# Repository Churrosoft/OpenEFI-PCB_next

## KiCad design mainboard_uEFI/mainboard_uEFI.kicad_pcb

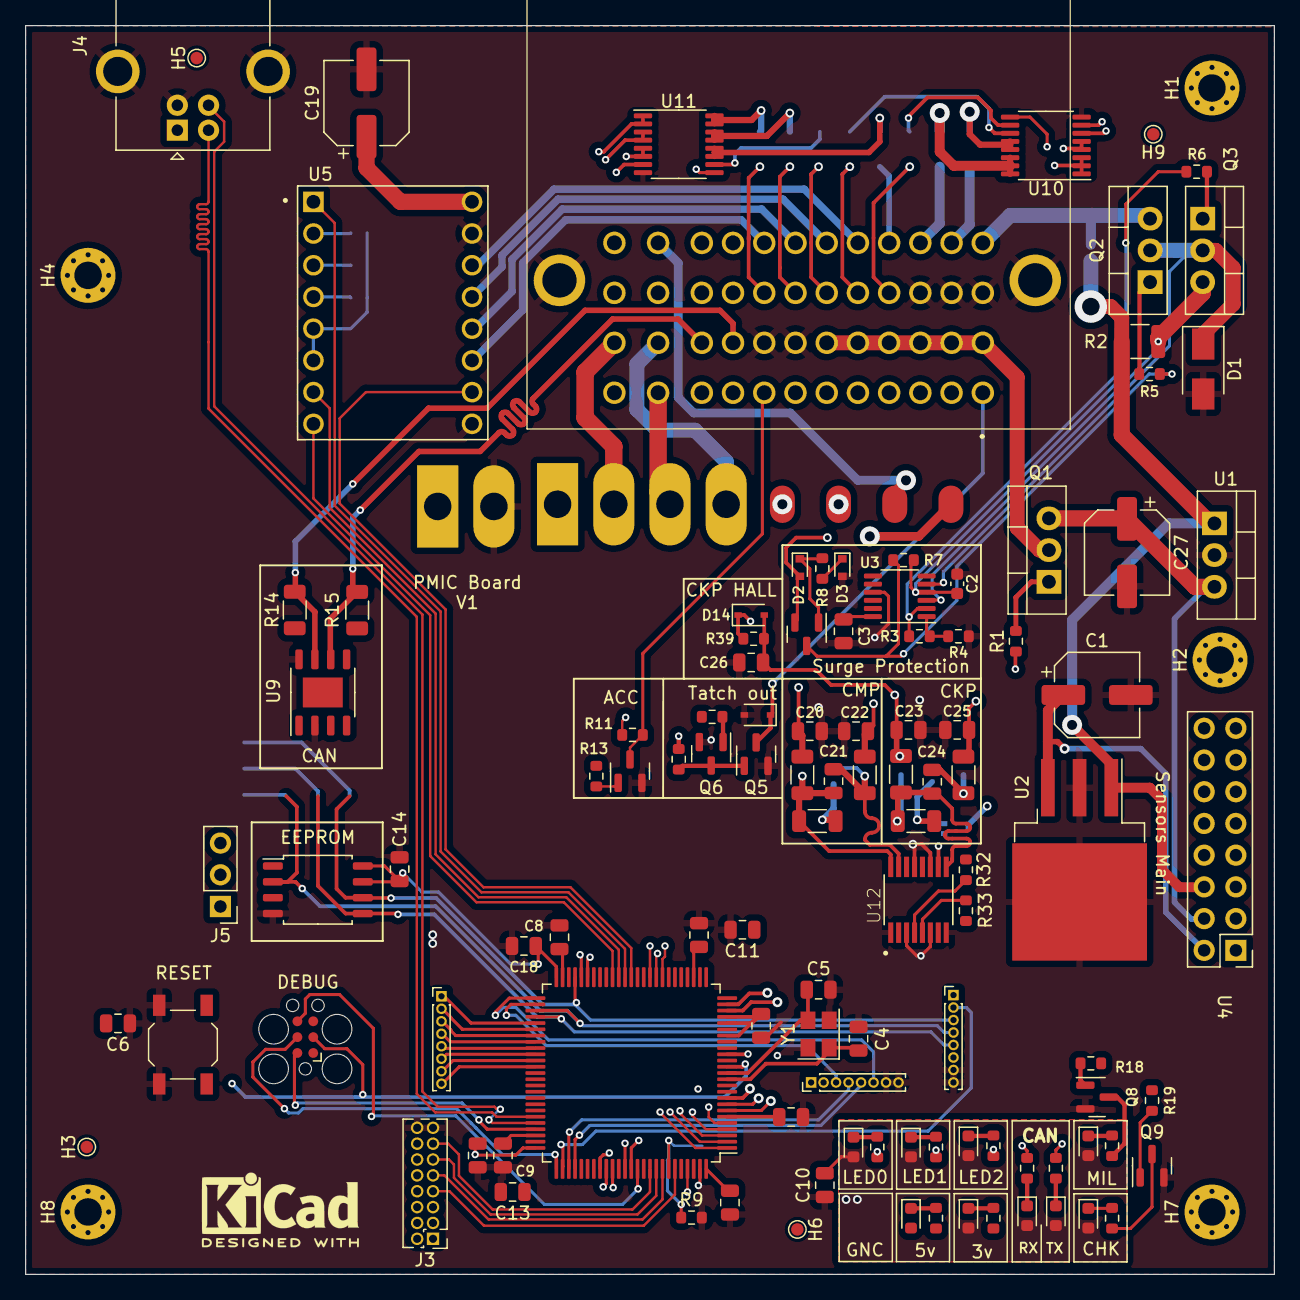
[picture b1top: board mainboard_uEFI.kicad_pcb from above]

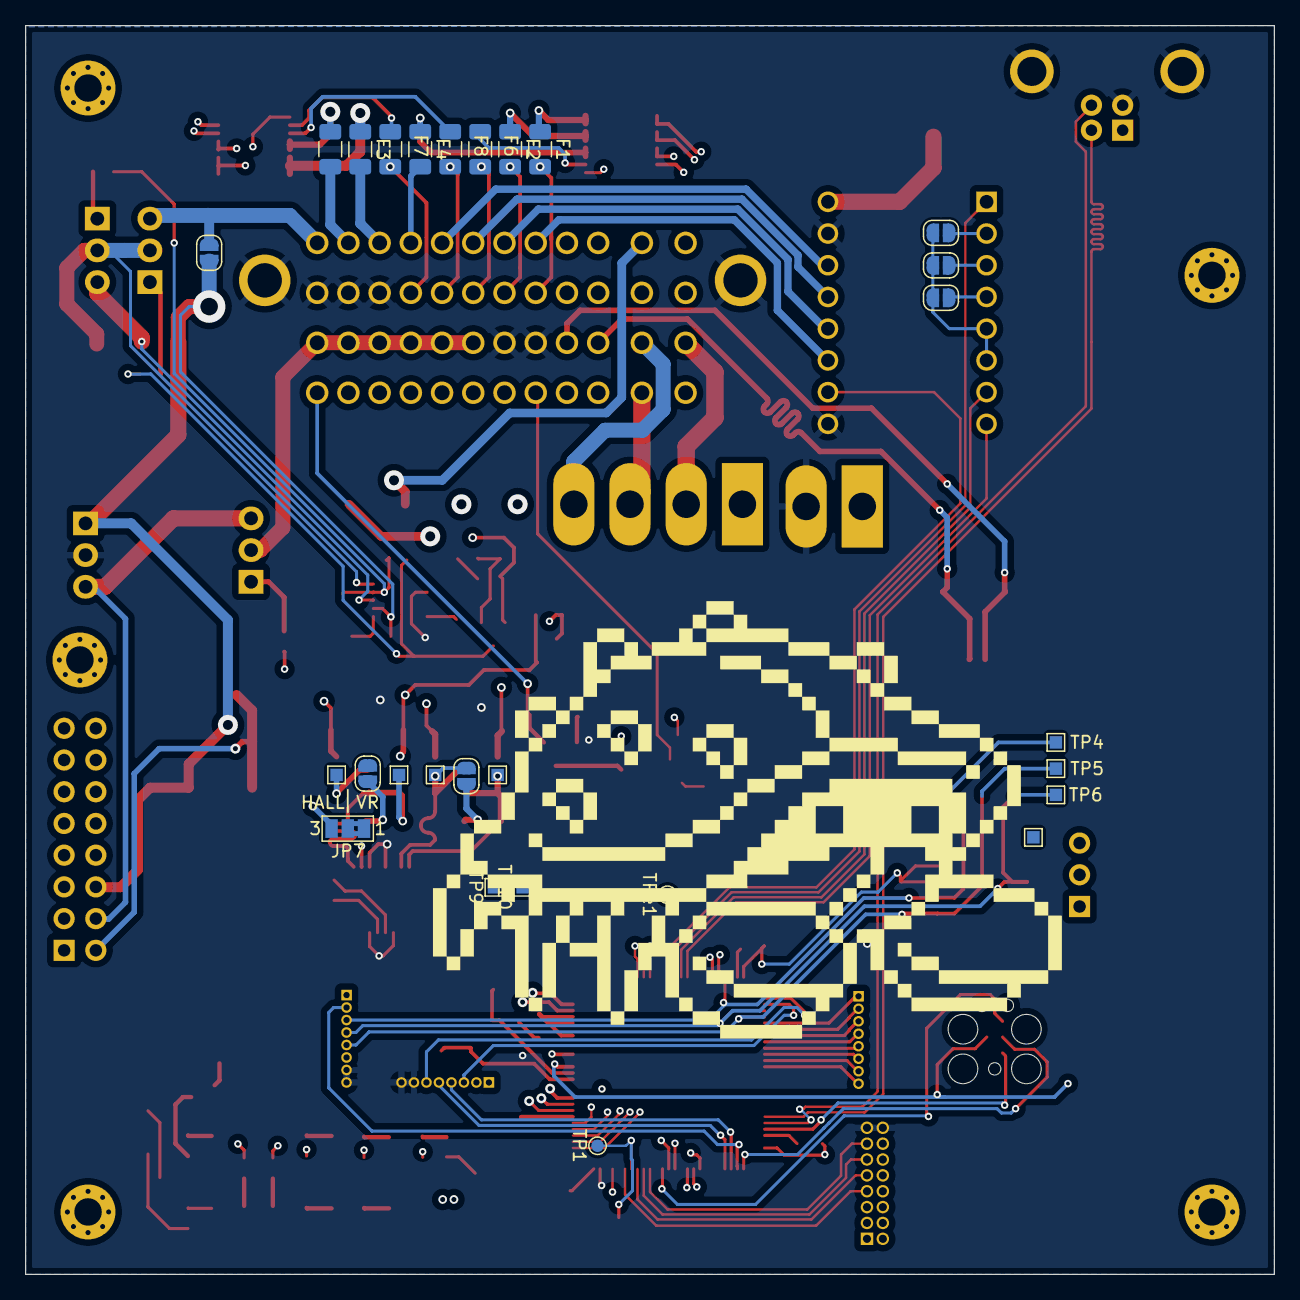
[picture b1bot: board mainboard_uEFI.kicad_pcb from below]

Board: 4 copper layers, 100.0 x 100.0 mm, 141 parts (27 on the bottom side), 143 nets.

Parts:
C1, C19, C27: 100uF ±20% 35V; CP_Elec_6.3x7.7
C2: 47nF; C_0603_1608Metric
C3, C6, C7, C10, C12, C13, C14, C15, C16, C17: 100nF; C_0805_2012Metric
C4, C5: 15pF; C_0805_2012Metric
C8, C9: 2.2uF; C_0805_2012Metric
C11: 1uF; C_0805_2012Metric
C18: 4.7uF; C_0805_2012Metric
C20, C21, C22, C23, C24, C25, C26: 0.01uF; C_0805_2012Metric
D1: SMAJ58CA; D_SMA
D2, D3: 1N4148; D_SOD-523
D4: MM3Z24VT1G; D_SOD-323
D5, D6, D7, D8, D9, D10, D11, D12, D13: LED; LED_0603_1608Metric
D14: K26; D_SOD-323
F1, F2, F3, F4, F5, F6, F7, F8: 750mA; Fuse_1206_3216Metric
H1, H2, H4, H7, H8: MountingHole; MountingHole_2.2mm_M2_Pad_Via
H3, H5, H6, H9: MountingHole; TestPoint_Pad_D1.0mm
J1: 36638-0002; 366380002
J2: Tag connect; Tag-Connect_TC2030-IDC-FP_2x03_P1.27mm_Vertical
J3: Conn_02x08_Odd_Even; PinHeader_2x08_P1.27mm_Vertical
J4: USB_B; USB_B_OST_USB-B1HSxx_Horizontal
J5: Conn_01x03; PinHeader_1x03_P2.54mm_Vertical
JP1: Jumper_NO_Small; SolderJumper-2_P1.3mm_Open_RoundedPad1.0x1.5mm
JP2, JP3, JP4, JP5, JP6: SolderJumper_2_Open; SolderJumper-2_P1.3mm_Open_RoundedPad1.0x1.5mm
JP7: vr/hall; SolderJumper-3_P1.3mm_Bridged2Bar12_Pad1.0x1.5mm_NumberLabe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
Q1: IRF540N; TO-220-3_Vertical
Q2, Q3: IRLZ44N; TO-220-3_Vertical
Q4, Q6, Q8, Q9: SS8050; SOT-23
Q5, Q7: AO3400A; SOT-23
R1, R5, R6: 10R 1/10W; R_0603_1608Metric
R2: 0.01R; R_1210_3225Metric
R3: 57.6K 1/10W; R_0603_1608Metric
R4: 4.99K 1/10W; R_0603_1608Metric
R7: 1M 1/10W; R_0603_1608Metric
R8: 10K 1/10W; R_0603_1608Metric
R9, R11, R13, R32, R33, R39: 10k; R_0603_1608Metric
R10: 100k; R_0603_1608Metric
R12, R18, R19: 1k; R_0603_1608Metric
R14, R15: 120R; R_1206_3216Metric
R16, R17, R20, R21, R22, R23, R24, R25, R26: 4.7k; R_0603_1608Metric
R27, R30, R34, R37: 10K 1/2W; R_1206_3216Metric
R29, R36: 4.99K 1/2W; R_1206_3216Metric
SW1: SW_Push; SW_SPST_TL3342
SYM1: SYM_Hot_Small; KiCad-Logo2_5mm_SilkScreen
TP1: BOOT0; TestPoint_Pad_D1.0mm
TP2, TP4, TP5, TP6, TP7, TP8, TP9, TP10, TP11, TP12: TestPoint; TestPoint_Pad_1.0x1.0mm
TPe1: BOOT1; TestPoint_Pad_D1.0mm
U1: MIC2940A-5.0WT; TO-220-3_Vertical
U2: MIC2940A-3.3WU; TO-263-3_TabPin2
U3: LT4363IMS; MSOP-12_3x4mm_P0.65mm
U4: SensorsV1
U5: PaP_Driver_v1; IC_DRV8825_STEPPER_MOTOR_DRIVER_CARRIER
U6: 25LCxxx; SOIC-8_5.275x5.275mm_P1.27mm
U7: PMIC_V1; pmic_v1
U8: STM32F407VGTx; LQFP-100_14x14mm_P0.5mm
U9: TJA1042T3118; HTSOP-8-1EP_3.9x4.9mm_P1.27mm_EP2.4x3.2mm
U10, U11: TPL7407LAPWR; TSSOP-16_4.4x5mm_P0.65mm
U12: MAX9926UAEE+; SOP63P602X175-16N
Y1: 25MHz; Crystal_SMD_3225-4Pin_3.2x2.5mm

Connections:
5V_ENABLE: R1.1, U8.16 (PC1)
+3V3: C1.1, C7.1, C10.1, C11.1, C12.1, C13.1, C14.1, C15.1, C16.1, C17.1, C18.1, D5.2 (A), D6.2 (A), D8.2 (A), D9.2 (A), D10.2 (A), D11.2 (A), D12.2 (A), D13.2 (A), D14.1 (K), J2.1, J3.1, JP2.1 (A), JP3.1 (A), JP4.1 (A), R11.1, R32.1, R33.1, R39.1, U2.3 (OUT), U5.5 (RESET), U5.6 (SLEEP), U6.3 (~WP), U6.7 (~HOLD), U6.8 (VCC), U7.34 (3v3), U8.6 (VBAT), U8.11 (VDD), U8.19 (VDD), U8.21 (VREF+), U8.22 (VDDA), U8.28 (VDD), U8.50 (VDD), U8.75 (VDD), U8.100 (VDD), U9.5 (VIO)
+5V: C27.1, D7.2 (A), J3.2, Q1.3 (S), U1.3 (OUT), U9.3 (VCC), U12.14 (VCC)
+5VA: J1.A2, J1.B2, J1.C2, J1.D2, J1.E2, J1.F2, Q1.2 (D)
+12V: C19.1, JP1.2, R2.1, R3.1, R10.1, U1.1 (IN), U2.1 (IN), U3.2 (OUT), U5.16 (VMOT), U7.1 (12v), U7.19 (12v), U7.20 (12v), U10.9 (COM), U11.9 (COM)
+12VA: D2.2 (A), J1.A4, JP1.1, Q2.3 (S), Q4.2 (E)
/ACC_DET: R13.1, U8.80 (PC12)
/AUX_CS_1: J3.3, U8.45 (PE14)
/AUX_CS_2: J3.5, U8.46 (PE15)
/AUX_IN_1: J3.7, U8.95 (PB8)
/AUX_IN_2: J3.9, U8.93 (PB7)
/AUX_IN_3: J3.11, U8.92 (PB6)
/AUX_IN_4: J3.13, U8.91 (PB5)
/AUX_OUT_1: J3.10, U8.35 (PB0)
/AUX_OUT_2: J3.12, U8.34 (PC5)
/AUX_OUT_3: J3.14, U8.33 (PC4)
/CAN1_RX: U8.81 (PD0), U9.4 (RXD)
/CAN1_TX: U8.82 (PD1), U9.1 (TXD)
/CHK: Q9.3 (C), R17.2
/CHK_OUT: R19.1, U8.66 (PC9)
/CKP_D: JP7.2 (C), U8.63 (PC6)
/CKP_VR: JP7.1 (A), R32.2, TP9.1, U12.4 (COUT1)
/CMP: R33.2, TP10.1, U8.64 (PC7), U12.5 (COUT2)
/ECN1: U7.15 (0_c), U8.59 (PD12)
/ECN2: U7.16 (1_c), U8.60 (PD13)
/ECN3: U7.17 (2_c), U8.61 (PD14)
/ECN4: U7.18 (3_c), U8.62 (PD15)
/IN1_N: C21.2, JP5.1 (A), R30.2, TP8.1, U12.15 (IN1-)
/IN1_P: C21.1, R27.2, R29.1, TP7.1, U12.16 (IN1+)
/IN2+: C24.1, R34.2, R36.1, TP11.1, U12.9 (IN2+)
/IN2-: C24.2, JP6.1 (A), R37.2, TP12.1, U12.10 (IN2-)
/INY1: U7.11 (0_c), U8.55 (PD8)
/INY2: U7.12 (1_c), U8.56 (PD9)
/INY3: U7.13 (2_c), U8.57 (PD10)
/INY4: U7.14 (3_c), U8.58 (PD11)
/LED0: R22.2, U8.83 (PD2)
/LED1: R23.2, U8.84 (PD3)
/LED2: R24.2, U8.85 (PD4)
/LED_CAN_RX: R26.2, U8.87 (PD6)
/LED_CAN_TX: R25.2, U8.88 (PD7)
/MEMORY_CS: TP2.1, U6.1 (~CS), U8.44 (PE13)
/MIL: Q8.3 (C), R16.2
/MIL_OUT: R18.1, U8.65 (PC8), U10.7 (IN7)
/MTR_DIR: U5.8 (DIR), U8.41 (PE10)
/MTR_ENABLE: U5.1 (ENABLE), U8.39 (PE8)
/MTR_FAULT: U5.10 (FAULT), U8.38 (PE7)
/MTR_STEP: U5.7 (STEP), U8.40 (PE9)
/NRST: C6.2, J2.3, SW1.1, U8.14 (NRST)
/PMIC_CS: U7.33 (SPI_CS), U8.77 (PA15)
/PMIC_ENABLE: U7.24 (ENABLE), U8.51 (PB12)
/PMIC_MAXI: U7.23 (MAXI), U8.79 (PC11)
/PMIC_NOMI: U7.22 (NOMI), U8.78 (PC10)
/PMIC_SPARK: U7.21 (SPARK), U8.52 (PB13)
/PWM | Relays /CHECK_ENGINE: F8.1, U10.11 (OUT6)
/PWM | Relays /MIL_OUT: F7.1, U10.10 (OUT7)
/PWM | Relays /R3_OUT: F6.1, U11.10 (OUT7)
/RPM_OUT: R12.1, U8.42 (PE11)
/R_AAC: U8.3 (PE4), U11.1 (IN1), U11.2 (IN2)
/R_ECN_INY: U8.1 (PE2), U11.5 (IN5), U11.6 (IN6)
/R_GNC_GLP: U8.2 (PE3), U11.3 (IN3), U11.4 (IN4)
/R_LMB: U8.97 (PE0), U11.7 (IN7)
/SPI2_MISO: J3.6, J5.3, TP6.1, U6.2 (MISO), U7.31 (SPI_MISO), U8.53 (PB14)
/SPI2_MOSI: J3.8, J5.2, TP5.1, U6.5 (MOSI), U7.30 (SPI_MOSI), U8.54 (PB15)
/SPI2_SCK: J3.4, J5.1, TP4.1, U6.6 (SCK), U7.32 (SPI_CLK), U8.47 (PB10)
/SYS_SWCLK: J2.4, U8.76 (PA14)
/SYS_SWDIO: J2.2, U8.72 (PA13)
/SYS_SWO: J2.6, U8.89 (PB3)
/TIM9_CH1: U8.4 (PE5), U10.1 (IN1), U10.2 (IN2), U10.3 (IN3)
/TIM9_CH2: U8.5 (PE6), U10.4 (IN4), U10.5 (IN5)
/USB_D+: J4.3 (D+), U8.71 (PA12)
/USB_D-: J4.2 (D-), U8.70 (PA11)
/VBUS: J4.1 (VBUS), U8.68 (PA9)
A1: D4.1 (K), J1.A1, Q5.3 (D)
B4: F5.2, J1.B4
C4: F3.2, J1.C4
CAN+: J1.J2, R14.2, U9.7 (CANH)
CAN-: J1.K2, R15.2, U9.6 (CANL)
CKP+: C23.1, C26.1, D14.2 (A), J1.K4, JP7.3 (B), R34.1, R39.2
CKP-: C25.1, J1.J4, R37.1
CMP+: C20.1, J1.K3, R27.1
CMP-: C22.1, J1.J3, R30.1
D3: F7.2, J1.D3
D4: F4.2, J1.D4
E3: F8.2, J1.E3
E4: J1.E4, U5.14 (B2)
F3: F6.2, J1.F3
F4: J1.F4, U5.13 (B1)
G3: F2.2, J1.G3
G4: J1.G4, U5.12 (A1)
GND: C1.2, C2.2, C3.2, C4.2, C5.2, C6.1, C7.2, C8.2, C9.2, C10.2, C11.2, C12.2, C13.2, C14.2, C15.2, C16.2, C17.2, C18.2, C19.2, C20.2, C22.2, C23.2, C25.2, C26.2, C27.2, D1.2 (A2), D3.2 (A), D4.2 (A), J1.A3, J1.B3, J1.C3, J1.G2, J1.H2, J1.MH1, J1.MH2, J2.5, J3.15, J3.16, J4.4 (GND), J4.5 (Shield), Q5.2 (S), Q6.2 (E), Q7.2 (S), Q8.2 (E), Q9.2 (E), R4.1, R9.2, R20.2, R21.2, SW1.2, U1.2 (GND), U2.2 (GND), U3.9 (GND), U5.9 (GND), U5.15 (GND), U6.4 (GND), U7.2 (GND), U7.25 (GND), U7.26 (GND), U7.27 (GND), U7.28 (GND), U8.10 (VSS), U8.20 (VSSA), U8.27 (VSS), U8.74 (VSS), U8.99 (VSS), U9.2 (GND), U9.8 (STB), U10.8 (GND), U11.8 (GND), U12.1 (INT_THRS1), U12.3 (BIAS1), U12.6 (BIAS2), U12.8 (INT_THRS2), U12.11 (GND), U12.13 (ZERO_EN), Y1.2, Y1.4
H1: J1.H1, Q7.3 (D), R11.2
H3: F1.2, J1.H3
H4: J1.H4, U5.11 (A2)
L1: J1.L1, U7.5 (2)
L2: J1.L2, U7.6 (3)
L3: J1.L3, U7.10 (3)
L4: J1.L4, U7.9 (2)
M1: J1.M1, U7.3 (0)
M2: J1.M2, U7.4 (1)
M3: J1.M3, U7.8 (1)
M4: J1.M4, U7.7 (0)
unnamed: C2.1, R6.2, R7.1, U3.4 (GATE)
unnamed: C3.1, U3.12 (TMR)
unnamed: C8.1, U8.49 (VCAP_1)
unnamed: C9.1, U8.73 (VCAP_2)
unnamed: D1.1 (A1), Q2.2 (D), Q3.2 (D), U3.5 (VCC)
unnamed: D2.1 (K), Q4.1 (B), R8.1
unnamed: D3.1 (K), R8.2
unnamed: D5.1 (K), R16.1
unnamed: D6.1 (K), R17.1
unnamed: D7.1 (K), R20.1
unnamed: D8.1 (K), R21.1
unnamed: D9.1 (K), R22.1
unnamed: D10.1 (K), R23.1
unnamed: D11.1 (K), R24.1
unnamed: D12.1 (K), R25.1
unnamed: D13.1 (K), R26.1
unnamed: F1.1, U11.15 (OUT2), U11.16 (OUT1)
unnamed: F2.1, U11.13 (OUT4), U11.14 (OUT3)
unnamed: F3.1, U10.14 (OUT3), U10.15 (OUT2), U10.16 (OUT1)
unnamed: F4.1, U11.11 (OUT6), U11.12 (OUT5)
unnamed: F5.1, U10.12 (OUT5), U10.13 (OUT4)
unnamed: JP2.2 (B), U5.2 (M0)
unnamed: JP3.2 (B), U5.3 (M1)
unnamed: JP4.2 (B), U5.4 (M2)
unnamed: JP5.2 (B), R29.2
unnamed: JP6.2 (B), R36.2
unnamed: Q1.1 (G), R1.2
unnamed: Q2.1 (G), R5.1
unnamed: Q3.1 (G), R6.1
unnamed: Q3.3 (S), R2.2, U3.3 (SNS)
unnamed: Q4.3 (C), R5.2, R7.2
unnamed: Q5.1 (G), Q6.3 (C), R10.2
unnamed: Q6.1 (B), R12.2
unnamed: Q7.1 (G), R13.2
unnamed: Q8.1 (B), R18.2
unnamed: Q9.1 (B), R19.2
unnamed: R3.2, R4.2, U3.1 (FB)
unnamed: R9.1, TP1.1, U8.94 (BOOT0)
unnamed: R14.1, R15.1
unnamed: TPe1.1, U8.37 (PB2)
OSC_IN: C4.1, U8.12 (PH0), Y1.1
OSC_OUT: C5.1, U8.13 (PH1), Y1.3

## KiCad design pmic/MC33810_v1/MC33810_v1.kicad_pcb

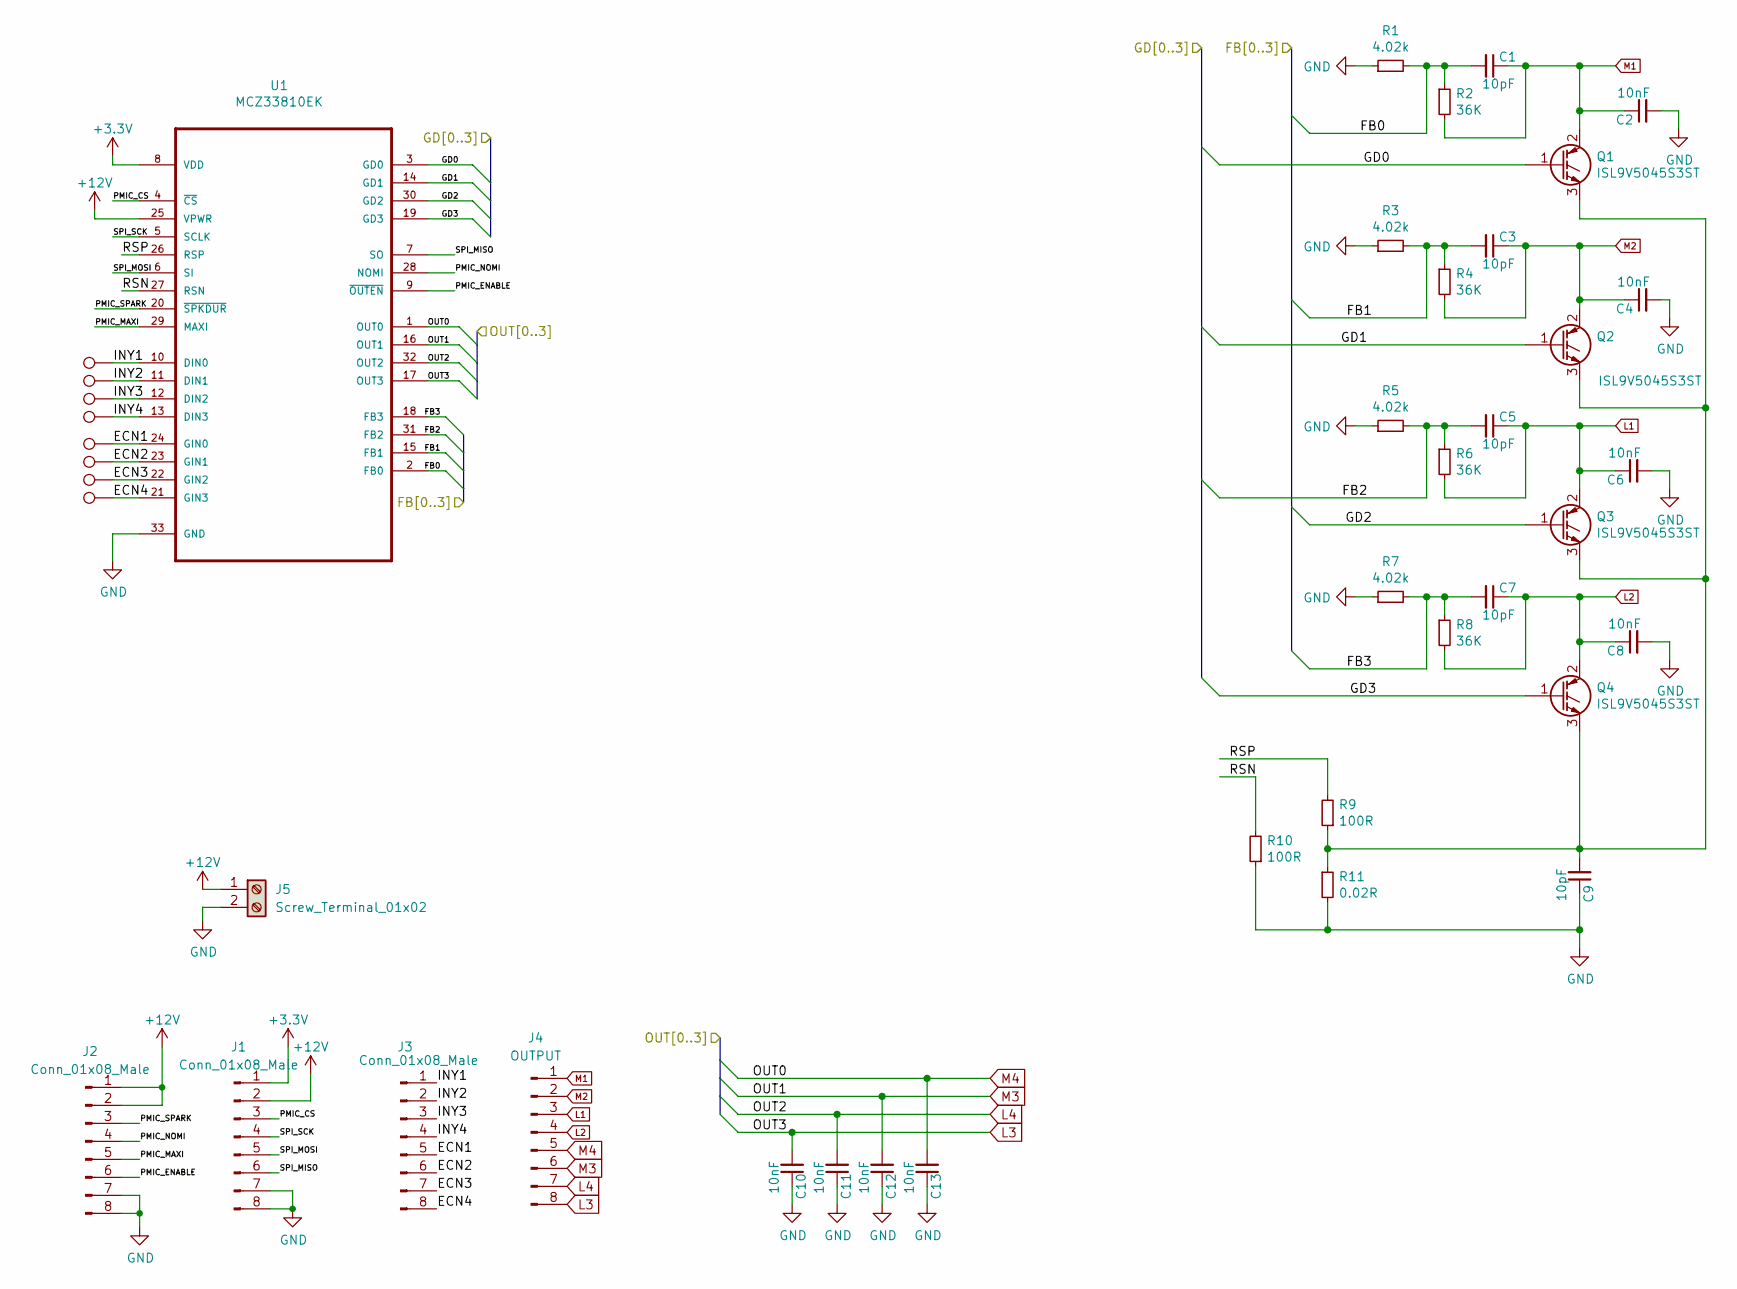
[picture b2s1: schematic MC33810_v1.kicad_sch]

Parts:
C1, C3, C5, C7: 10pF; C_0603_1608Metric; LCSC C106245
C2, C4, C6, C8, C10, C11, C12, C13: 10nF; C_0603_1608Metric; LCSC C100042
C9: 10pF; C_0603_1608Metric
J1, J2, J3: Conn_01x08_Male; PinHeader_1x08_P1.00mm_Vertical
J4: OUTPUT; TerminalBlock_Dinkle_DT-55-B01X-08_P10.00mm
J5: Screw_Terminal_01x02; TerminalBlock_Dinkle_DT-55-B01X-02_P10.00mm
Q1, Q2, Q3, Q4: ISL9V5045S3ST; TO-263-2
R1, R3, R5, R7: 4.02k; R_0603_1608Metric; LCSC C23040
R2, R4, R6, R8: 36K; R_0603_1608Metric; LCSC C192548
R9, R10: 100R; R_0603_1608Metric; LCSC C159890
R11: 0.02R; R_2512_6332Metric; LCSC C326611
TP1, TP2, TP3, TP4, TP5, TP6, TP7, TP8: TestPoint; TestPoint_Pad_1.0x1.0mm
U1: MCZ33810EK; SOP65P1030X245-33N

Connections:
+3V3: J1.1, U1.8 (VDD)
+12V: J1.2, J2.1, J2.2, J5.1, U1.25 (VPWR)
/ECN1: J3.5, TP5.1, U1.24 (GIN0)
/ECN2: J3.6, TP6.1, U1.23 (GIN1)
/ECN3: J3.7, TP7.1, U1.22 (GIN2)
/ECN4: J3.8, TP8.1, U1.21 (GIN3)
/FB0: C1.2, R1.2, R2.1, U1.2 (FB0)
/FB1: C3.2, R3.2, R4.1, U1.15 (FB1)
/FB2: C5.2, R5.2, R6.1, U1.31 (FB2)
/FB3: C7.2, R7.2, R8.1, U1.18 (FB3)
/GD0: Q1.1 (G), U1.3 (GD0)
/GD1: Q2.1 (G), U1.14 (GD1)
/GD2: Q3.1 (G), U1.30 (GD2)
/GD3: Q4.1 (G), U1.19 (GD3)
/INY1: J3.1, TP1.1, U1.10 (DIN0)
/INY2: J3.2, TP2.1, U1.11 (DIN1)
/INY3: J3.3, TP3.1, U1.12 (DIN2)
/INY4: J3.4, TP4.1, U1.13 (DIN3)
/PMIC_CS: J1.3, U1.4 (~CS)
/PMIC_ENABLE: J2.6, U1.9 (~OUTEN)
/PMIC_MAXI: J2.5, U1.29 (MAXI)
/PMIC_NOMI: J2.4, U1.28 (NOMI)
/PMIC_SPARK: J2.3, U1.20 (~SPKDUR)
/RSN: R10.2, U1.27 (RSN)
/RSP: R9.2, U1.26 (RSP)
/SPI_MISO: J1.6, U1.7 (SO)
/SPI_MOSI: J1.5, U1.6 (SI)
/SPI_SCK: J1.4, U1.5 (SCLK)
GND: C2.2, C4.2, C6.2, C8.2, C9.1, C10.1, C11.1, C12.1, C13.1, J1.7, J1.8, J2.7, J2.8, J5.2, R1.1, R3.1, R5.1, R7.1, R10.1, R11.2, U1.33 (GND)
L1: C5.1, C6.1, J4.3, Q3.2 (C), R6.2
L2: C7.1, C8.1, J4.4, Q4.2 (C), R8.2
L3: C10.2, J4.8, U1.17 (OUT3)
L4: C11.2, J4.7, U1.32 (OUT2)
M1: C1.1, C2.1, J4.1, Q1.2 (C), R2.2
M2: C3.1, C4.1, J4.2, Q2.2 (C), R4.2
M3: C12.2, J4.6, U1.16 (OUT1)
M4: C13.2, J4.5, U1.1 (OUT0)
unnamed: C9.2, Q1.3 (E), Q2.3 (E), Q3.3 (E), Q4.3 (E), R9.1, R11.1

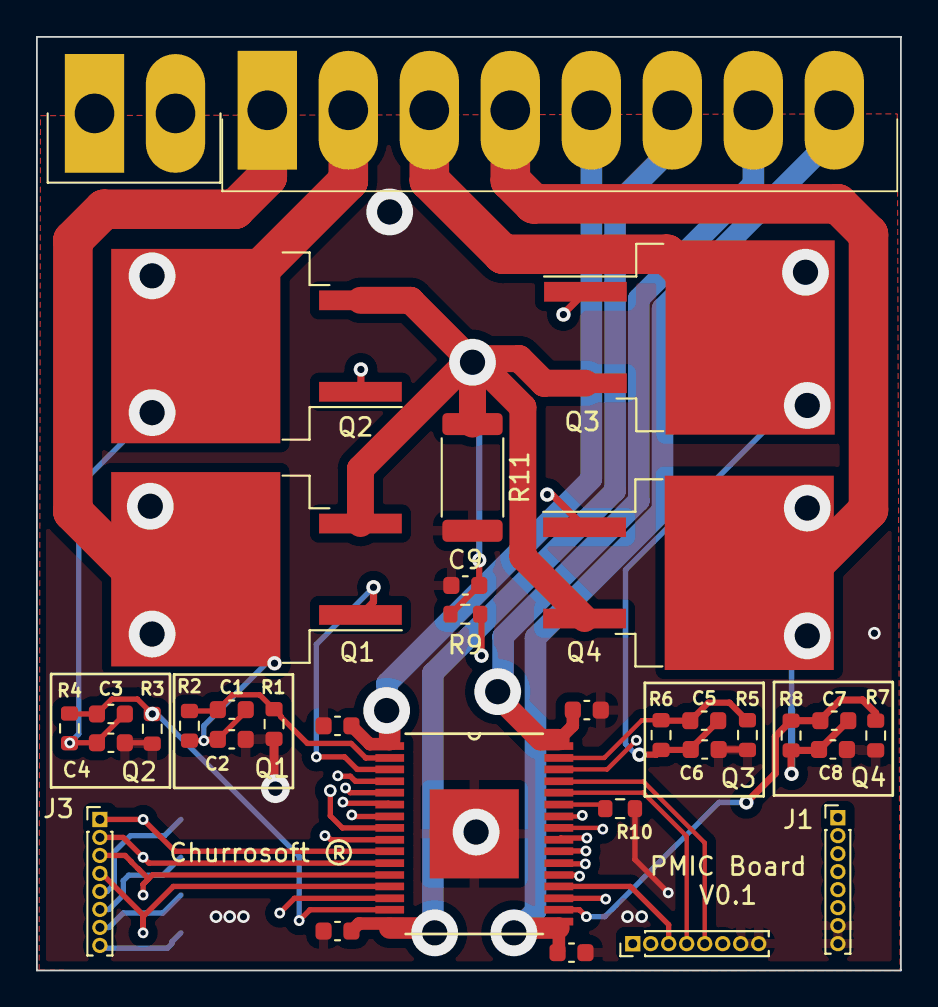
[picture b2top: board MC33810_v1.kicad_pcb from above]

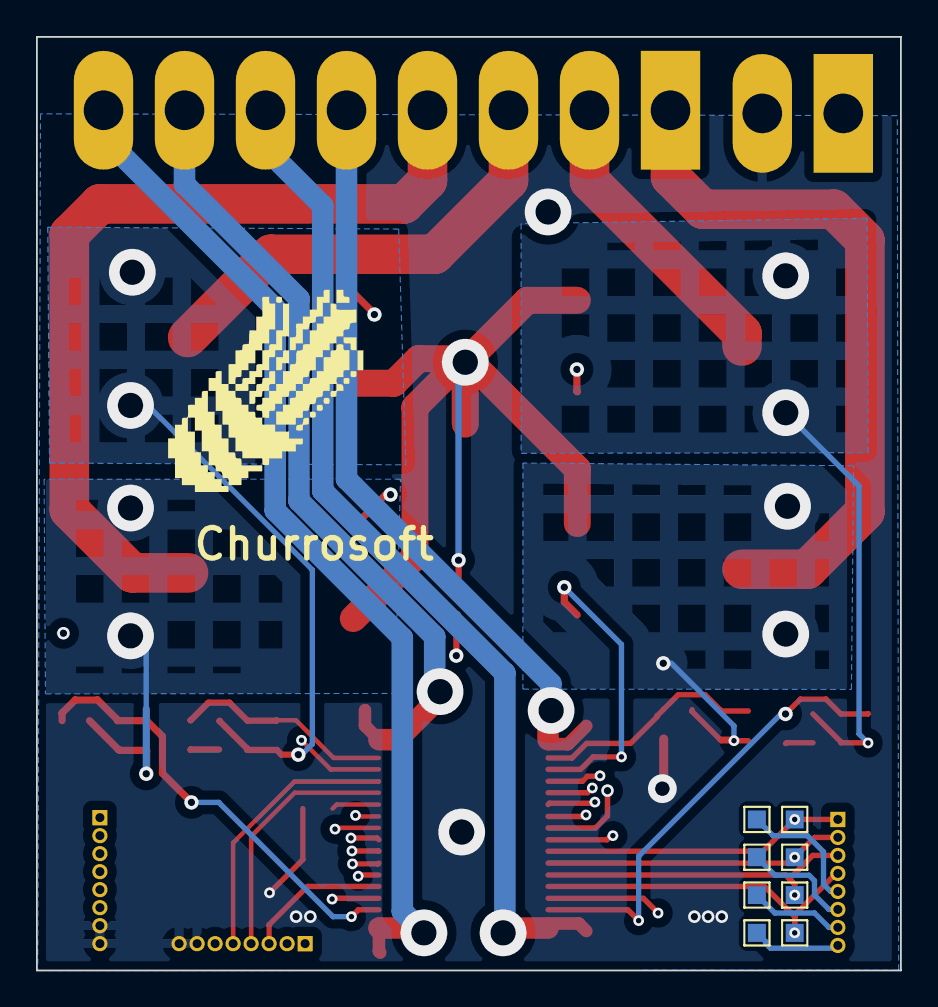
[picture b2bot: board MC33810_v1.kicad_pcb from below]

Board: 4 copper layers, 48.0 x 51.9 mm, 43 parts (9 on the bottom side), 38 nets.

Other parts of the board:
Churrosoft: SYM_Hot_Large; churro_new_v4

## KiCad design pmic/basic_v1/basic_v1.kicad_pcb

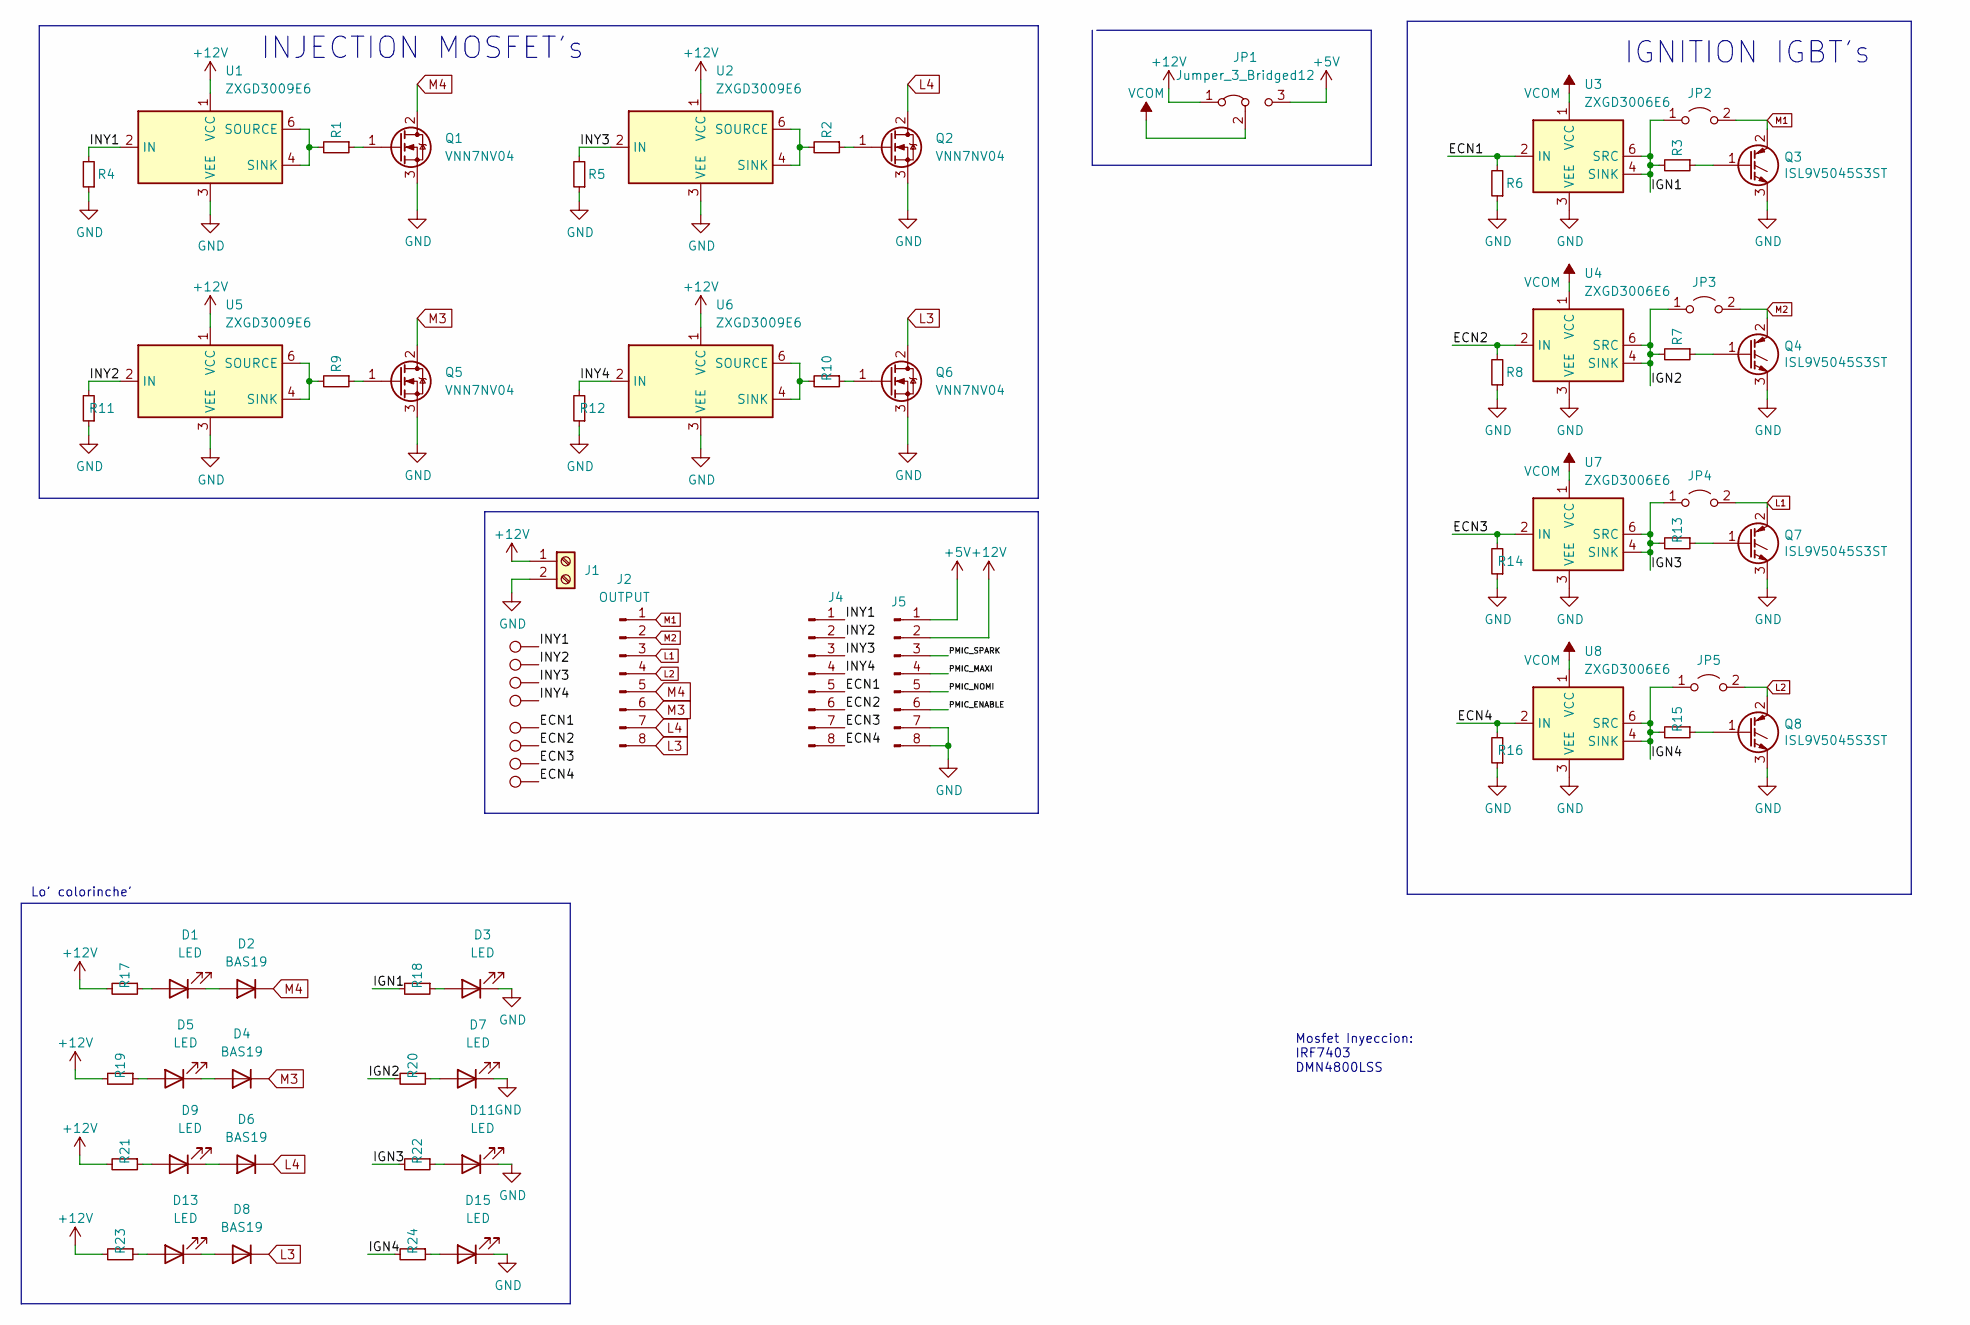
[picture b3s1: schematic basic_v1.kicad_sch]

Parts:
D1, D3, D5, D7, D9, D11, D13, D15: LED; LED_0603_1608Metric
D2, D4, D6, D8: BAS19; SOT-23; LCSC C8661
J1: Screw_Terminal_01x02; TerminalBlock_Dinkle_DT-55-B01X-02_P10.00mm
J2: OUTPUT; hipower_8pin
J4, J5: Conn_01x08_Male; PinHeader_1x08_P1.00mm_Vertical
JP1: Jumper_3_Bridged12; PinHeader_1x03_P2.54mm_Vertical
JP2, JP3, JP4, JP5: Jumper_2_Open; SolderJumper-2_P1.3mm_Open_RoundedPad1.0x1.5mm
Q1, Q2, Q5, Q6: VNN7NV04; TO-252-2; LCSC C155605
Q3, Q4, Q7, Q8: ISL9V5045S3ST; TO-263-2
R1, R2, R3, R7, R9, R10, R13, R15: 22R; R_0805_2012Metric
R4, R5, R6, R8, R11, R12, R14, R16: 100k 1/10W +-1%; R_0603_1608Metric; LCSC C217840
R17, R18, R19, R20, R21, R22, R23, R24: 680R; R_0603_1608Metric; LCSC C217840
TP1, TP2, TP3, TP4, TP5, TP6, TP7, TP8: TestPoint; TestPoint_Pad_1.0x1.0mm
U1, U2, U5, U6: ZXGD3009E6; SOT-23-6
U3, U4, U7, U8: ZXGD3006E6; SOT-23-6

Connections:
+5V: J5.1, JP1.3 (B)
+12V: J1.1, J5.2, JP1.1 (A), R17.2, R19.2, R21.2, R23.2, U1.1 (VCC), U2.1 (VCC), U5.1 (VCC), U6.1 (VCC)
/ECN1: J4.5, R6.2, TP5.1, U3.2 (IN)
/ECN2: J4.6, R8.2, TP6.1, U4.2 (IN)
/ECN3: J4.7, R14.2, TP7.1, U7.2 (IN)
/ECN4: J4.8, R16.2, TP8.1, U8.2 (IN)
/IGN1: JP2.1 (A), R3.2, R18.2, U3.4 (SINK), U3.6 (SRC)
/IGN2: JP3.1 (A), R7.2, R20.2, U4.4 (SINK), U4.6 (SRC)
/IGN3: JP4.1 (A), R13.2, R22.2, U7.4 (SINK), U7.6 (SRC)
/IGN4: JP5.1 (A), R15.2, R24.2, U8.4 (SINK), U8.6 (SRC)
/INY1: J4.1, R4.2, TP1.1, U1.2 (IN)
/INY2: J4.2, R11.2, TP2.1, U5.2 (IN)
/INY3: J4.3, R5.2, TP3.1, U2.2 (IN)
/INY4: J4.4, R12.2, TP4.1, U6.2 (IN)
/PMIC_ENABLE: J5.6
/PMIC_MAXI: J5.4
/PMIC_NOMI: J5.5
/PMIC_SPARK: J5.3
GND: D3.1 (K), D7.1 (K), D11.1 (K), D15.1 (K), J1.2, J5.7, J5.8, Q1.3 (S), Q2.3 (S), Q3.3 (E), Q4.3 (E), Q5.3 (S), Q6.3 (S), Q7.3 (E), Q8.3 (E), R4.1, R5.1, R6.1, R8.1, R11.1, R12.1, R14.1, R16.1, U1.3 (VEE), U2.3 (VEE), U3.3 (VEE), U4.3 (VEE), U5.3 (VEE), U6.3 (VEE), U7.3 (VEE), U8.3 (VEE)
L1: J2.3, JP4.2 (B), Q7.2 (C)
L2: J2.4, JP5.2 (B), Q8.2 (C)
L3: D8.3 (K), J2.8, Q6.2 (D)
L4: D6.3 (K), J2.7, Q2.2 (D)
M1: J2.1, JP2.2 (B), Q3.2 (C)
M2: J2.2, JP3.2 (B), Q4.2 (C)
M3: D4.3 (K), J2.6, Q5.2 (D)
M4: D2.3 (K), J2.5, Q1.2 (D)
unnamed: D1.1 (K), D2.1 (A)
unnamed: D1.2 (A), R17.1
unnamed: D3.2 (A), R18.1
unnamed: D4.1 (A), D5.1 (K)
unnamed: D5.2 (A), R19.1
unnamed: D6.1 (A), D9.1 (K)
unnamed: D7.2 (A), R20.1
unnamed: D9.2 (A), R21.1
unnamed: D11.2 (A), R22.1
unnamed: D8.1 (A), D13.1 (K)
unnamed: D13.2 (A), R23.1
unnamed: D15.2 (A), R24.1
unnamed: Q1.1 (G), R1.1
unnamed: Q2.1 (G), R2.1
unnamed: Q3.1 (G), R3.1
unnamed: Q4.1 (G), R7.1
unnamed: Q5.1 (G), R9.1
unnamed: Q6.1 (G), R10.1
unnamed: Q7.1 (G), R13.1
unnamed: Q8.1 (G), R15.1
unnamed: R1.2, U1.4 (SINK), U1.6 (SOURCE)
unnamed: R2.2, U2.4 (SINK), U2.6 (SOURCE)
unnamed: R9.2, U5.4 (SINK), U5.6 (SOURCE)
unnamed: R10.2, U6.4 (SINK), U6.6 (SOURCE)
VCOM: JP1.2 (C), U3.1 (VCC), U4.1 (VCC), U7.1 (VCC), U8.1 (VCC)

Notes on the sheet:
Lo' colorinche'
IGNITION IGBT's
INJECTION MOSFET's
Mosfet Inyeccion: IRF7403 DMN4800LSS

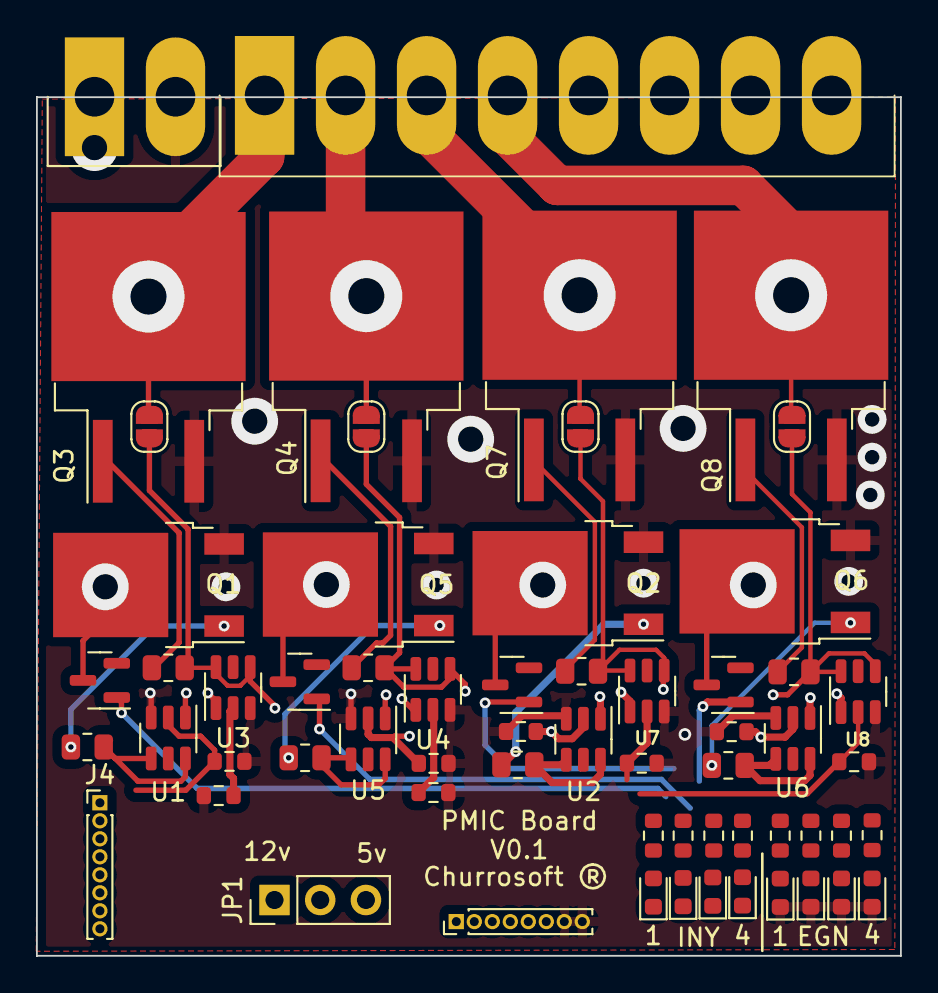
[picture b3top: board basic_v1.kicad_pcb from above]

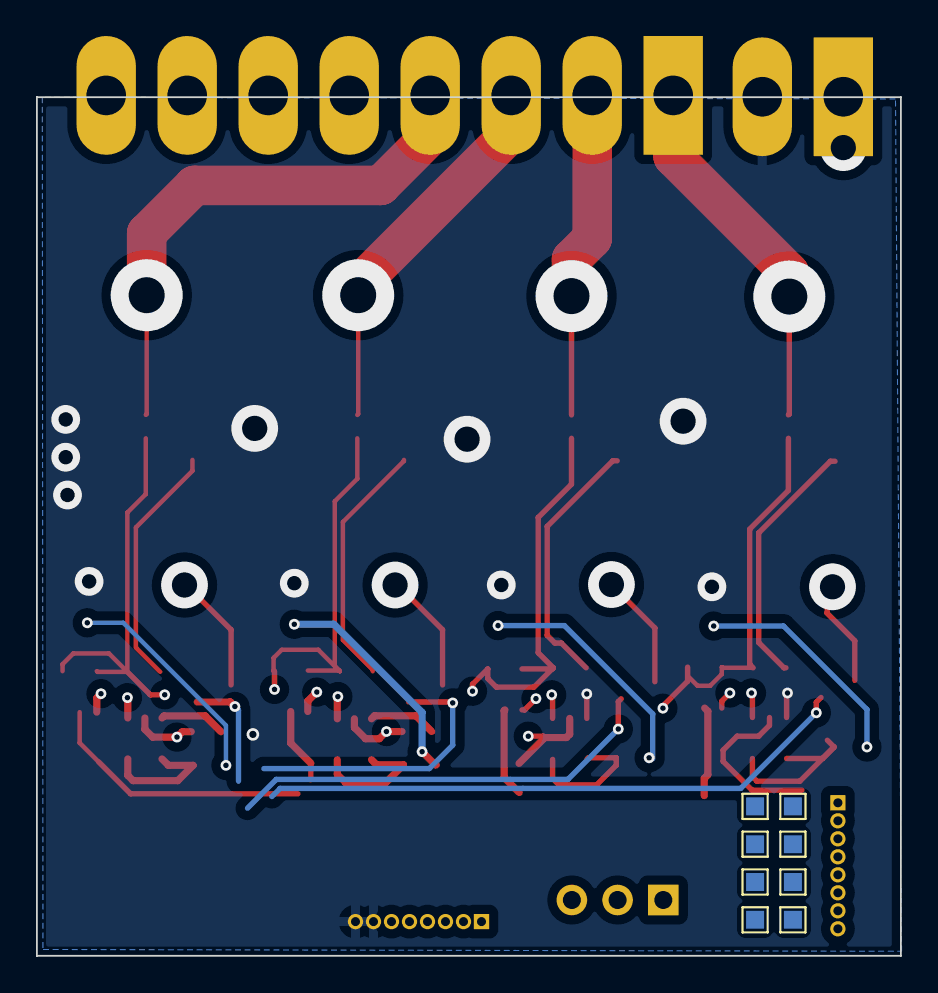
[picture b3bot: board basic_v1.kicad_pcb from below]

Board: 4 copper layers, 48.0 x 47.7 mm, 69 parts (8 on the bottom side), 48 nets.
